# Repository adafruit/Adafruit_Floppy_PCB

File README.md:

# Adafruit_Floppy_PCB
PCB files for flippy floppys

Untested (as of now) - probably wont work yet

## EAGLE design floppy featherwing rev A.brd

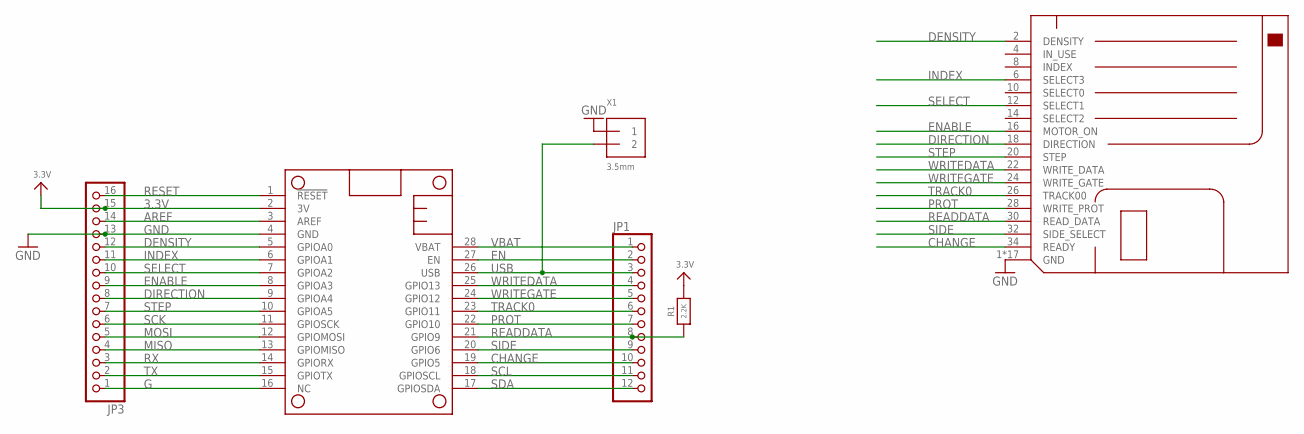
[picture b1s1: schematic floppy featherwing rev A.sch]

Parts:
FDD1: FLOPPY_IDC_SHROUDED; 2X17_FLOPPY_IDC
JP1: HEADER-1X12; 1X12_ROUND
JP3: HEADER-1X16ROUND; 1X16_ROUND
MS1: FEATHERWING
R1: 2.2K; 0805-NO
X1: 3.5mm; TERMBLOCK_1X2-3.5MM

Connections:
3.3V: JP3.15, MS1.2 (3V), R1.2
AREF: JP3.14, MS1.3 (AREF)
CHANGE: FDD1.34 (READY), JP1.10, MS1.19 (GPIO5)
DENSITY: FDD1.2 (DENSITY), JP3.12, MS1.5 (GPIOA0)
DIRECTION: FDD1.18 (DIRECTION), JP3.8, MS1.9 (GPIOA4)
EN: JP1.2, MS1.27 (EN)
ENABLE: FDD1.16 (MOTOR_ON), JP3.9, MS1.8 (GPIOA3)
G: JP3.1, MS1.16 (NC)
GND: FDD1.1 (GND), FDD1.3 (GND), FDD1.5 (GND), FDD1.7 (GND), FDD1.9 (GND), FDD1.11 (GND), FDD1.13 (GND), FDD1.15 (GND), FDD1.17 (GND), FDD1.19 (GND), FDD1.21 (GND), FDD1.23 (GND), FDD1.25 (GND), FDD1.27 (GND), FDD1.29 (GND), FDD1.31 (GND), FDD1.33 (GND), JP3.13, MS1.4 (GND), X1.1
INDEX: FDD1.6 (SELECT3), JP3.11, MS1.6 (GPIOA1)
MISO: JP3.4, MS1.13 (GPIOMISO)
MOSI: JP3.5, MS1.12 (GPIOMOSI)
PROT: FDD1.28 (WRITE_PROT), JP1.7, MS1.22 (GPIO10)
READDATA: FDD1.30 (READ_DATA), JP1.8, MS1.21 (GPIO9), R1.1
RESET: JP3.16, MS1.1 (!RESET)
RX: JP3.3, MS1.14 (GPIORX)
SCK: JP3.6, MS1.11 (GPIOSCK)
SCL: JP1.11, MS1.18 (GPIOSCL)
SDA: JP1.12, MS1.17 (GPIOSDA)
SELECT: FDD1.12 (SELECT1), JP3.10, MS1.7 (GPIOA2)
SIDE: FDD1.32 (SIDE_SELECT), JP1.9, MS1.20 (GPIO6)
STEP: FDD1.20 (STEP), JP3.7, MS1.10 (GPIOA5)
TRACK0: FDD1.26 (TRACK00), JP1.6, MS1.23 (GPIO11)
TX: JP3.2, MS1.15 (GPIOTX)
USB: JP1.3, MS1.26 (USB), X1.2
VBAT: JP1.1, MS1.28 (VBAT)
WRITEDATA: FDD1.22 (WRITE_DATA), JP1.4, MS1.25 (GPIO13)
WRITEGATE: FDD1.24 (WRITE_GATE), JP1.5, MS1.24 (GPIO12)

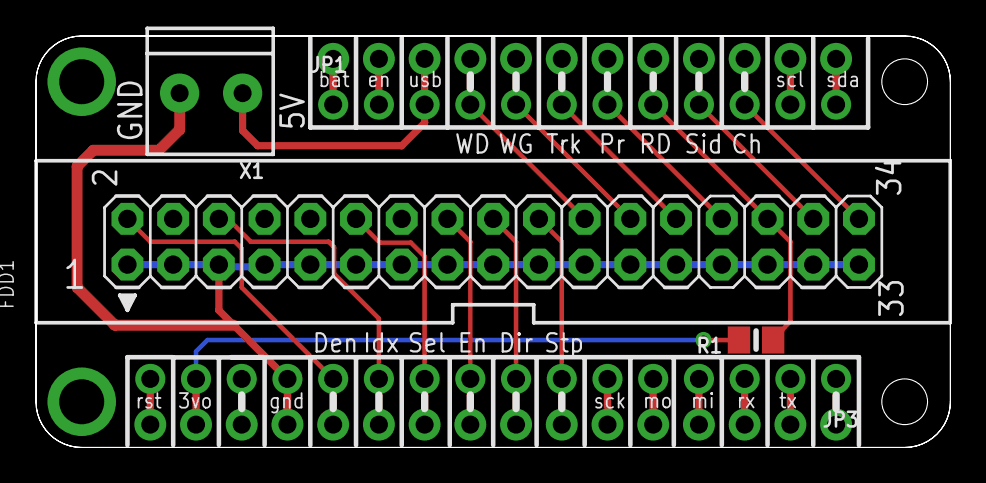
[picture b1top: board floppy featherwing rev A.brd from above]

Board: 2 copper layers, 50.8 x 22.9 mm, 6 parts (0 on the bottom side), 28 nets.

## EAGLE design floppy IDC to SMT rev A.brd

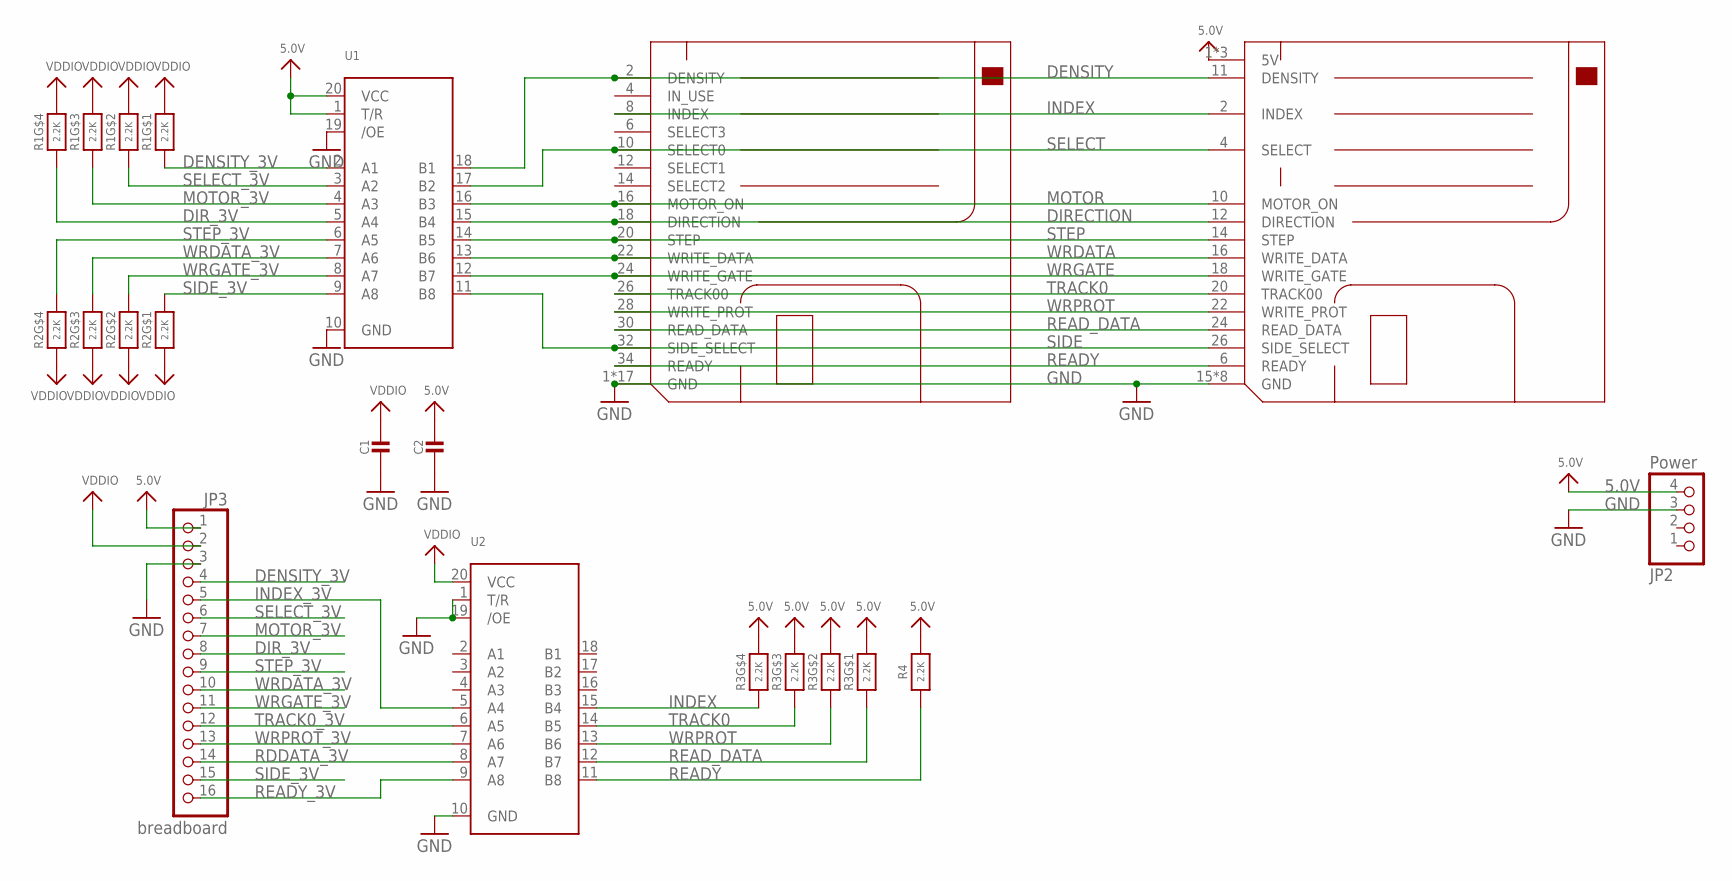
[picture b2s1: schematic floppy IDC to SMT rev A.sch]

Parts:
C1, C2: CAP_CERAMIC0805-NOOUTLINE; 0805-NO
FDD1: FLOPPY_IDC_SHROUDED; 2X17_FLOPPY_IDC
FDD2: FLOPPY_FPC; FPC_26P_1MM
JP2: Power; 1X04/90
JP3: breadboard; 1X16
R1, R2, R3: 2.2K; RESPACK_4X0603
R4: 2.2K; 0603-NO
U1, U2: 74LCX245; TSSOP20

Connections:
5.0V: C2.1, FDD2.1 (5V), FDD2.3 (5V), FDD2.5 (5V), JP2.4, JP3.1, R3.5 (2), R3.6 (2), R3.7 (2), R3.8 (2), R4.2, U1.1 (T/R), U1.20 (VCC)
DENSITY: FDD1.2 (DENSITY), FDD2.11 (DENSITY), U1.18 (B1)
DENSITY_3V: JP3.4, R1.1, U1.2 (A1)
DIRECTION: FDD1.18 (DIRECTION), FDD2.12 (DIRECTION), U1.15 (B4)
DIR_3V: JP3.8, R1.4 (1), U1.5 (A4)
GND: C1.2, C2.2, FDD1.1 (GND), FDD1.3 (GND), FDD1.5 (GND), FDD1.7 (GND), FDD1.9 (GND), FDD1.11 (GND), FDD1.13 (GND), FDD1.15 (GND), FDD1.17 (GND), FDD1.19 (GND), FDD1.21 (GND), FDD1.23 (GND), FDD1.25 (GND), FDD1.27 (GND), FDD1.29 (GND), FDD1.31 (GND), FDD1.33 (GND), FDD2.15 (GND), FDD2.17 (GND), FDD2.19 (GND), FDD2.21 (GND), FDD2.23 (GND), FDD2.25 (GND), FDD2.M1 (GND), FDD2.M2 (GND), JP2.3, JP3.3, U1.10 (GND), U1.19 (/OE), U2.1 (T/R), U2.10 (GND), U2.19 (/OE)
INDEX: FDD1.8 (INDEX), FDD2.2 (INDEX), R3.4 (1), U2.15 (B4)
INDEX_3V: JP3.5, U2.5 (A4)
MOTOR: FDD1.16 (MOTOR_ON), FDD2.10 (MOTOR_ON), U1.16 (B3)
MOTOR_3V: JP3.7, R1.3 (1), U1.4 (A3)
RDDATA_3V: JP3.14, U2.8 (A7)
READY: FDD1.34 (READY), FDD2.6 (READY), R4.1, U2.11 (B8)
READY_3V: JP3.16, U2.9 (A8)
READ_DATA: FDD1.30 (READ_DATA), FDD2.24 (READ_DATA), R3.1, U2.12 (B7)
SELECT: FDD1.10 (SELECT0), FDD2.4 (SELECT), U1.17 (B2)
SELECT_3V: JP3.6, R1.2 (1), U1.3 (A2)
SIDE: FDD1.32 (SIDE_SELECT), FDD2.26 (SIDE_SELECT), U1.11 (B8)
SIDE_3V: JP3.15, R2.8 (2), U1.9 (A8)
STEP: FDD1.20 (STEP), FDD2.14 (STEP), U1.14 (B5)
STEP_3V: JP3.9, R2.5 (2), U1.6 (A5)
TRACK0: FDD1.26 (TRACK00), FDD2.20 (TRACK00), R3.3 (1), U2.14 (B5)
TRACK0_3V: JP3.12, U2.6 (A5)
VDDIO: C1.1, JP3.2, R1.5 (2), R1.6 (2), R1.7 (2), R1.8 (2), R2.1, R2.2 (1), R2.3 (1), R2.4 (1), U2.20 (VCC)
WRDATA: FDD1.22 (WRITE_DATA), FDD2.16 (WRITE_DATA), U1.13 (B6)
WRDATA_3V: JP3.10, R2.6 (2), U1.7 (A6)
WRGATE: FDD1.24 (WRITE_GATE), FDD2.18 (WRITE_GATE), U1.12 (B7)
WRGATE_3V: JP3.11, R2.7 (2), U1.8 (A7)
WRPROT: FDD1.28 (WRITE_PROT), FDD2.22 (WRITE_PROT), R3.2 (1), U2.13 (B6)
WRPROT_3V: JP3.13, U2.7 (A6)

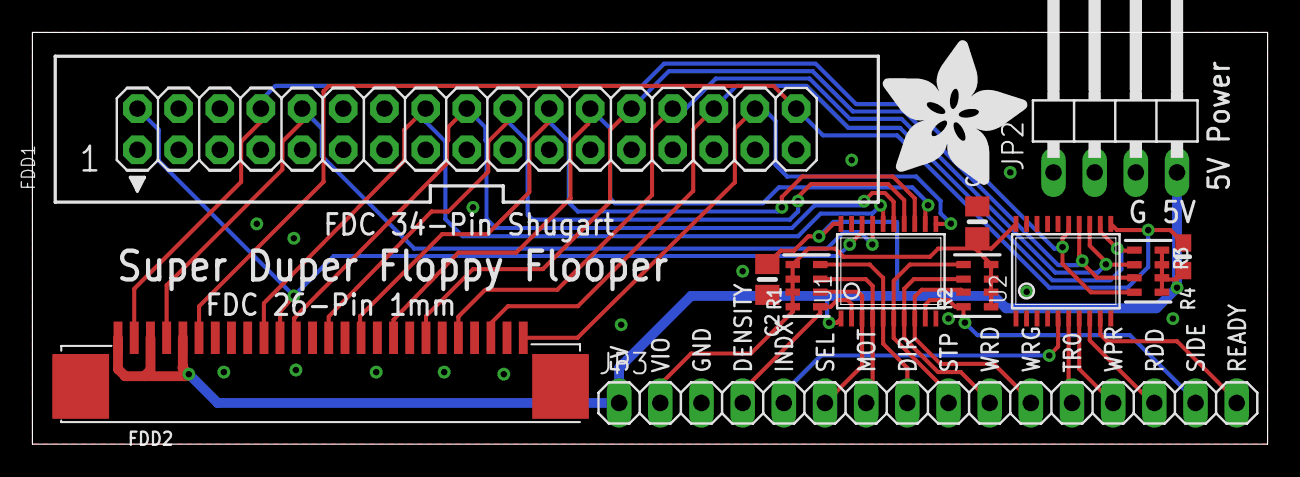
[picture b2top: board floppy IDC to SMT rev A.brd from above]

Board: 2 copper layers, 76.2 x 25.4 mm, 13 parts (0 on the bottom side), 29 nets.

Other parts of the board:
U$23: ADAFRUIT_9MM

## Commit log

2021-12-31 first draft of breadboard to floppy adapter friend
2021-12-31 fly away lil floppy wing!
2021-12-31 floppified
